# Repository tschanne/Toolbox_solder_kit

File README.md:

# Toolbox_solder_kit
A solder kit in the design of the Toolbox Bodensee club logo. https://toolbox-bodensee.de/
Desgined with KiCAD.

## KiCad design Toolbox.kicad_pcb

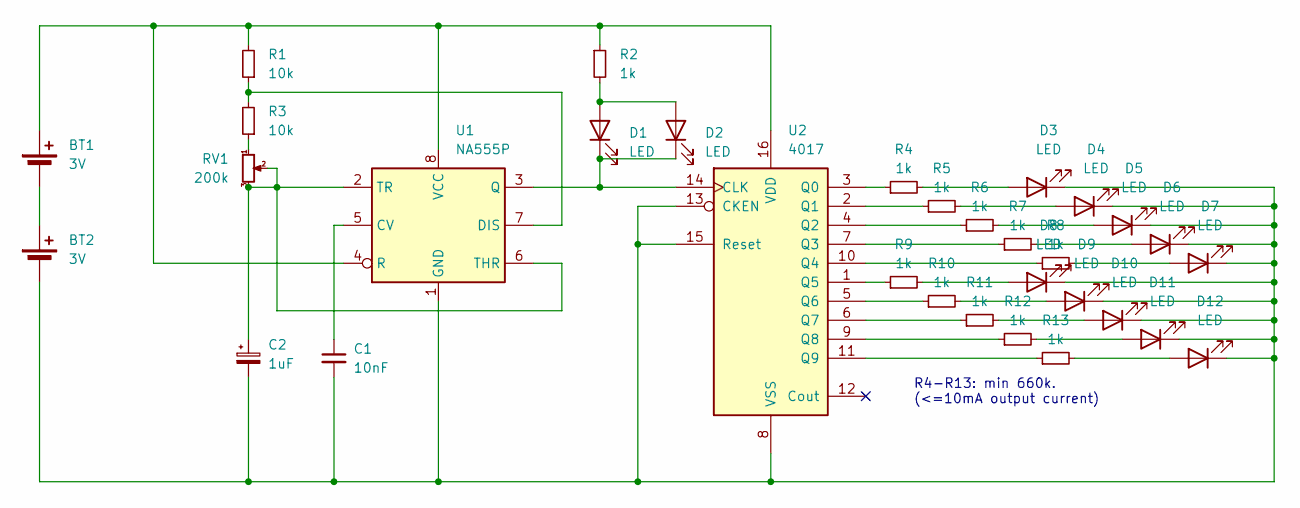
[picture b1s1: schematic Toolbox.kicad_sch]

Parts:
BT1, BT2: 3V; BatteryHolder_aliexpress_2025
C1: 10nF; C_Disc_D3.0mm_W2.0mm_P2.50mm
C2: 1uF; CP_Radial_D5.0mm_P2.50mm
D1: LED; LED_1206_3216Metric_Pad1.42x1.75mm_HandSolder
D2: LED; LED_D3.0mm
D3, D4, D5, D6, D7, D8, D9, D10, D11, D12: LED; LED_D5.0mm_double_sided
R1, R3: 10k; R_Axial_DIN0207_L6.3mm_D2.5mm_P10.16mm_Horizontal
R2, R4, R5, R6, R7, R8, R9, R10, R11, R12, R13: 1k; R_Axial_DIN0207_L6.3mm_D2.5mm_P10.16mm_Horizontal
RV1: 200k; Potentiometer_Runtron_RM-065_Vertical
U1: NA555P; DIP-8_W7.62mm
U2: 4017; DIP-16_W7.62mm_LongPads

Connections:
unnamed: BT1.1 (+), R1.2, R2.1, U1.4 (R), U1.8 (VCC), U2.16 (VDD)
unnamed: BT1.2 (-), BT2.1 (+)
unnamed: BT2.2 (-), C1.2, C2.2, D3.1 (K), D4.1 (K), D5.1 (K), D6.1 (K), D7.1 (K), D8.1 (K), D9.1 (K), D10.1 (K), D11.1 (K), D12.1 (K), U1.1 (GND), U2.8 (VSS), U2.13 (CKEN), U2.15 (Reset)
unnamed: D1.2 (A), D2.2 (A), R2.2
unnamed: D1.1 (K), D2.1 (K), U1.3 (Q), U2.14 (CLK)
unnamed: D3.2 (A), R4.2
unnamed: D4.2 (A), R5.2
unnamed: D5.2 (A), R6.2
unnamed: D6.2 (A), R7.2
unnamed: D7.2 (A), R8.2
unnamed: D8.2 (A), R9.2
unnamed: D9.2 (A), R10.2
unnamed: D10.2 (A), R11.2
unnamed: D11.2 (A), R12.2
unnamed: D12.2 (A), R13.2
unnamed: R3.1, RV1.1
unnamed: C1.1, U1.5 (CV)
unnamed: R1.1, R3.2, U1.7 (DIS)
unnamed: C2.1, RV1.2, RV1.3, U1.2 (TR), U1.6 (THR)
unnamed: R4.1, U2.3 (Q0)
unnamed: R5.1, U2.2 (Q1)
unnamed: R6.1, U2.4 (Q2)
unnamed: R7.1, U2.7 (Q3)
unnamed: R8.1, U2.10 (Q4)
unnamed: R9.1, U2.1 (Q5)
unnamed: R10.1, U2.5 (Q6)
unnamed: R11.1, U2.6 (Q7)
unnamed: R12.1, U2.9 (Q8)
unnamed: R13.1, U2.11 (Q9)

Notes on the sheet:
R4-R13: min 660k. (<=10mA output current)

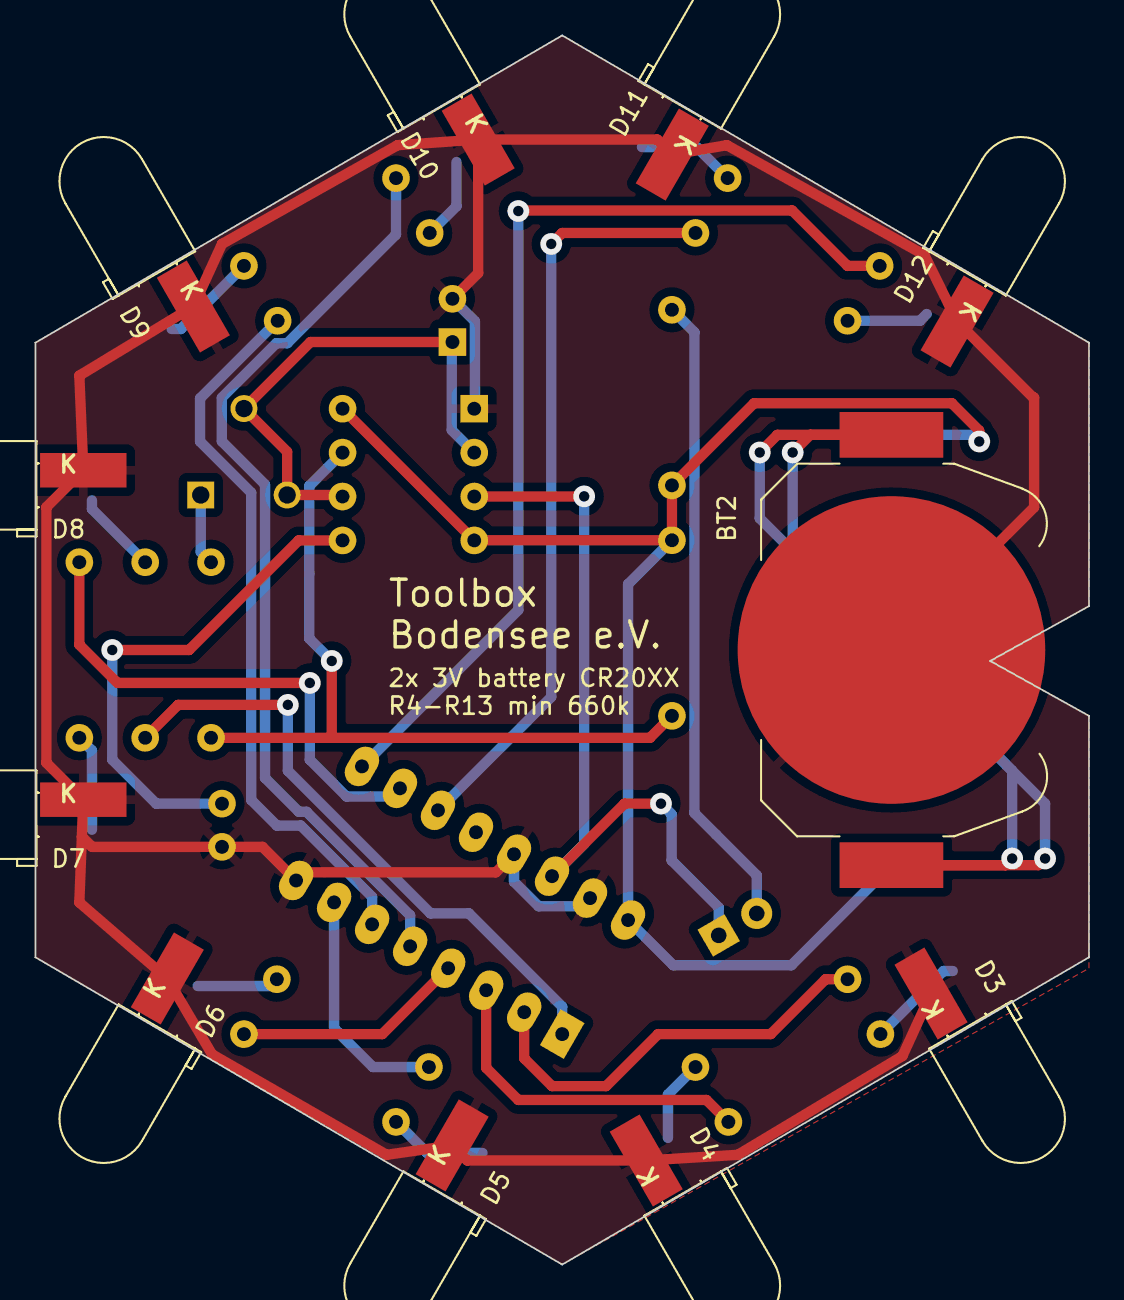
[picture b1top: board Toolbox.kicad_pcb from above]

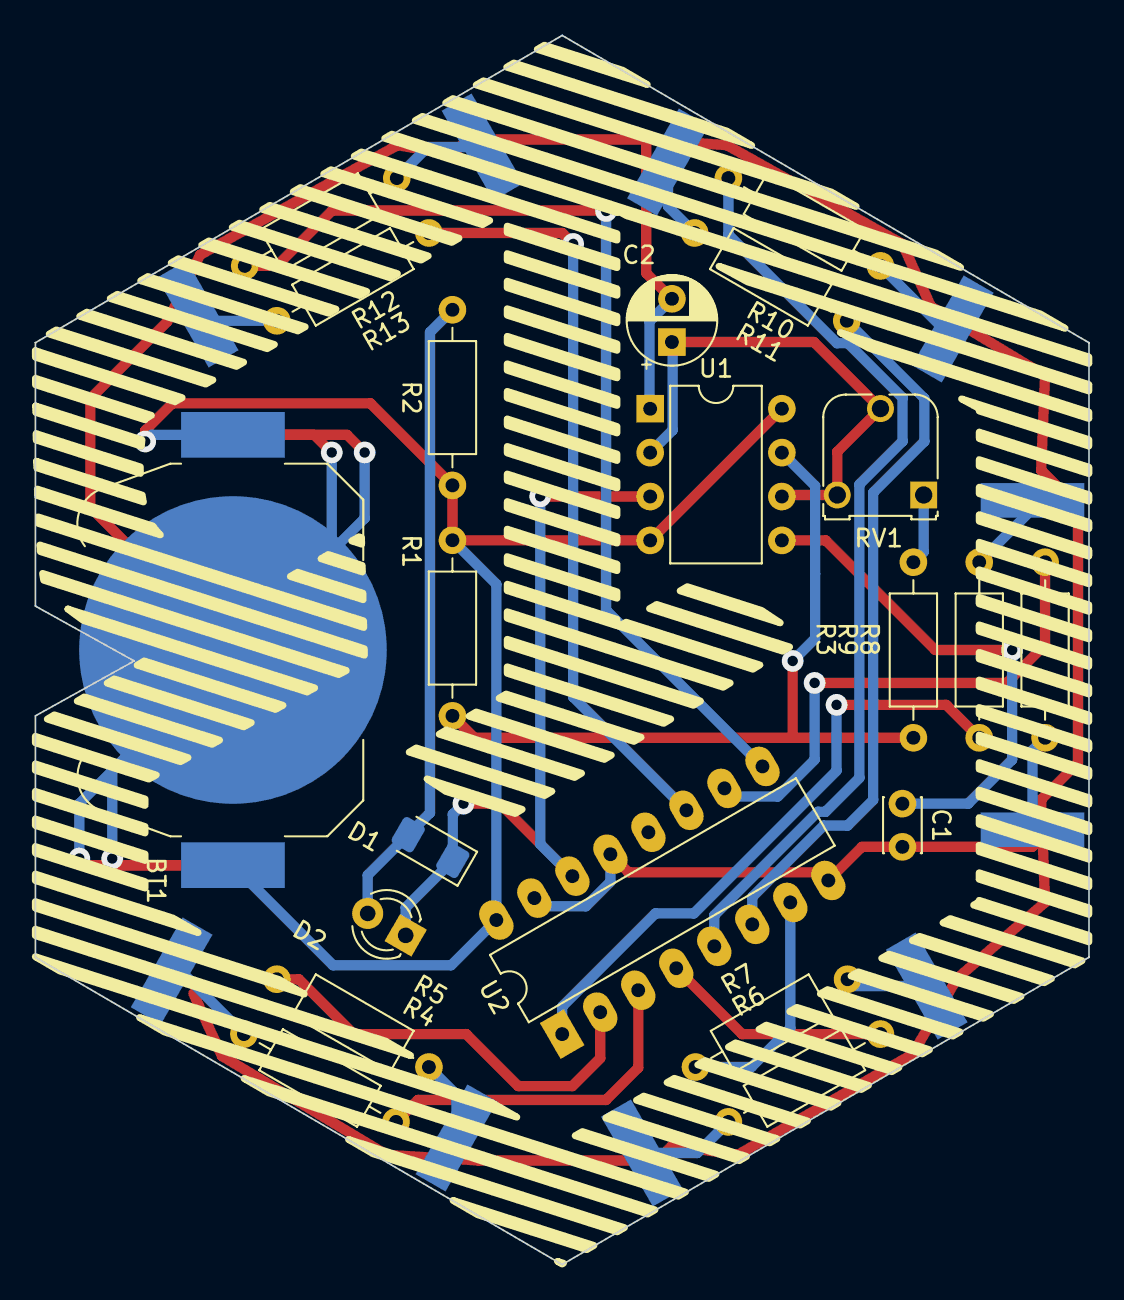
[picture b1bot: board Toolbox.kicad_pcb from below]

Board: 2 copper layers, 61.0 x 71.1 mm, 32 parts (21 on the bottom side), 29 nets.

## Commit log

2025-08-29 add folders
